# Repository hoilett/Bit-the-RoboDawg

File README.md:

# Bit-the-RoboDawg
Robot dog project

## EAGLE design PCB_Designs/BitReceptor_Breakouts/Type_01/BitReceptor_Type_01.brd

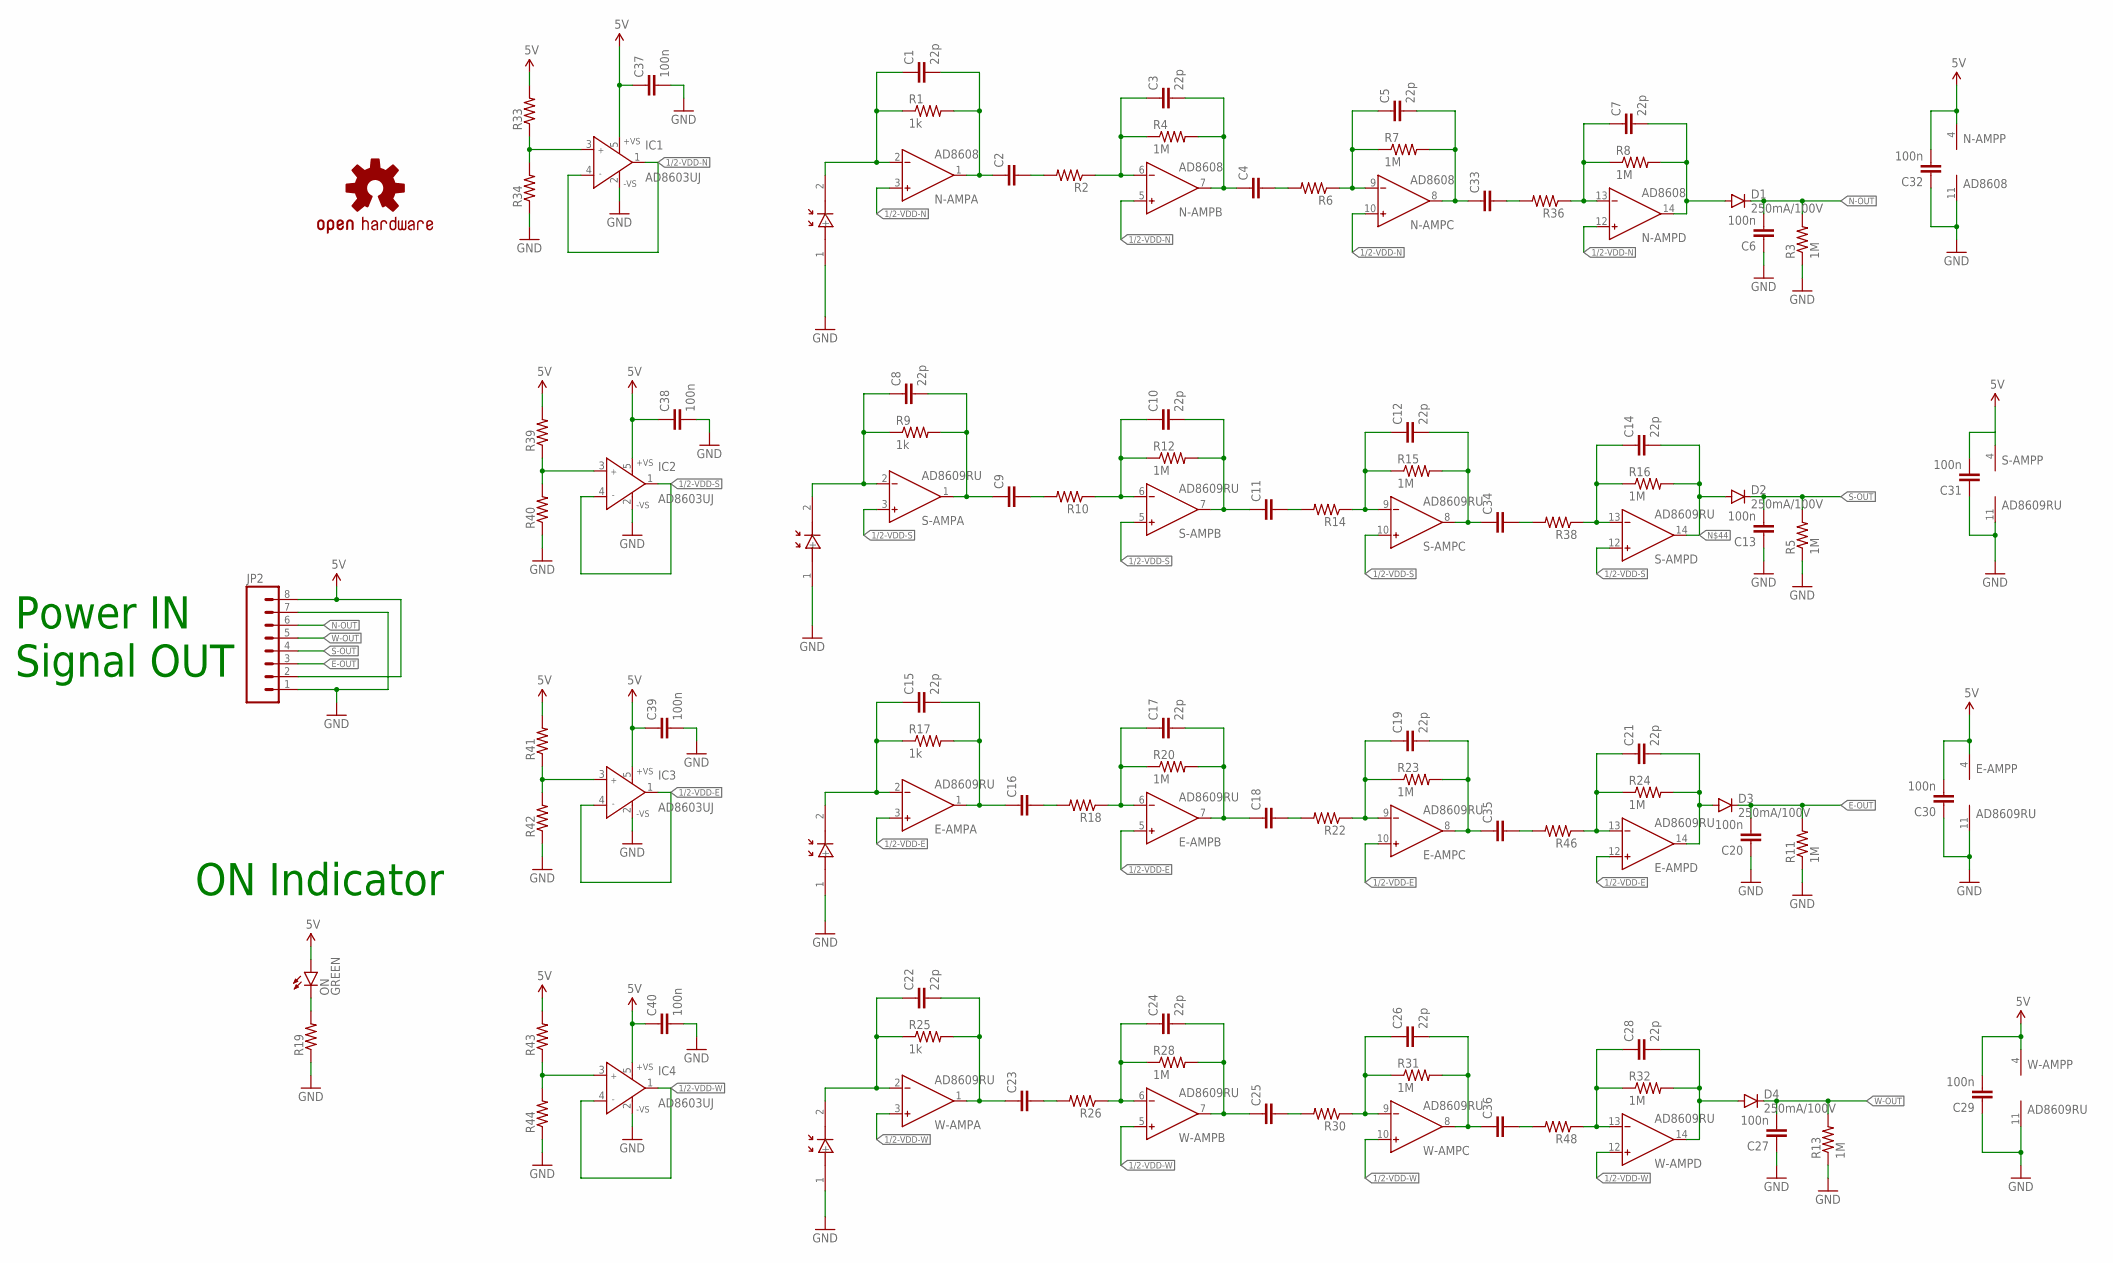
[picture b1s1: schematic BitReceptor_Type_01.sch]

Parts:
C1, C3, C5, C7, C8, C10, C12, C14, C15, C17, C19, C21, C22, C24, C26, C28: 22p; C0402
C2, C4, C9, C11, C16, C18, C23, C25, C33, C34, C35, C36: C-EUC0402; C0402
C6, C13, C20, C27, C29, C30, C31, C32, C37, C38, C39, C40: 100n; C0402
D1, D2, D3, D4: 250mA/100V; SOD-323
E-AMP: AD8609RU; TSSOP14
E-PD1: BPW46; PIN-PHOTODIODE
IC1, IC2, IC3, IC4: AD8603UJ; SOT23-5
JP2: M08NO_SILK; 1X08_PIN1_NO_SILK
LOGO1: OSHW-LOGOS; OSHW-LOGO-S
N-AMP: AD8608; TSSOP14
N-PD1: BPW46; PIN-PHOTODIODE
ON: GREEN; LED-0603
R1, R9, R17, R25: 1k; R0402
R2, R6, R10, R14, R18, R19, R22, R26, R30, R33, R34, R36, R38, R39, R40, R41, R42, R43, R44, R46, R48: R-US_R0402; R0402
R3, R4, R5, R7, R8, R11, R12, R13, R15, R16, R20, R23, R24, R28, R31, R32: 1M; R0402
S-AMP: AD8609RU; TSSOP14
S-PD1: BPW46; PIN-PHOTODIODE
W-AMP: AD8609RU; TSSOP14
W-PD1: BPW46; PIN-PHOTODIODE

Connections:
1/2-VDD-E: E-AMP.3 (IN+), E-AMP.5 (IN+), E-AMP.10 (IN+), E-AMP.12 (IN+), IC3.1 (OUT), IC3.4 (IN-)
1/2-VDD-N: IC1.1 (OUT), IC1.4 (IN-), N-AMP.3 (IN+), N-AMP.5 (IN+), N-AMP.10 (IN+), N-AMP.12 (IN+)
1/2-VDD-S: IC2.1 (OUT), IC2.4 (IN-), S-AMP.3 (IN+), S-AMP.5 (IN+), S-AMP.10 (IN+), S-AMP.12 (IN+)
1/2-VDD-W: IC4.1 (OUT), IC4.4 (IN-), W-AMP.3 (IN+), W-AMP.5 (IN+), W-AMP.10 (IN+), W-AMP.12 (IN+)
5V: C29.2, C30.2, C31.2, C32.2, C37.1, C38.1, C39.1, C40.1, E-AMP.4 (V+), IC1.5 (+VS), IC2.5 (+VS), IC3.5 (+VS), IC4.5 (+VS), JP2.2, JP2.8, N-AMP.4 (V+), ON.A, R33.2, R39.2, R41.2, R43.2, S-AMP.4 (V+), W-AMP.4 (V+)
E-OUT: C20.2, D3.C, JP2.3, R11.2
GND: C6.1, C13.1, C20.1, C27.1, C29.1, C30.1, C31.1, C32.1, C37.2, C38.2, C39.2, C40.2, E-AMP.11 (V-), E-PD1.1 (+), IC1.2 (-VS), IC2.2 (-VS), IC3.2 (-VS), IC4.2 (-VS), JP2.1, JP2.7, N-AMP.11 (V-), N-PD1.1 (+), R3.1, R5.1, R11.1, R13.1, R19.1, R34.1, R40.1, R42.1, R44.1, S-AMP.11 (V-), S-PD1.1 (+), W-AMP.11 (V-), W-PD1.1 (+)
unnamed: C1.1, N-AMP.2 (IN-), N-PD1.2 (-), R1.1
unnamed: C14.1, R16.1, R38.1, S-AMP.13 (IN-)
unnamed: C1.2, C2.1, N-AMP.1 (OUT), R1.2
unnamed: C8.1, R9.1, S-AMP.2 (IN-), S-PD1.2 (-)
unnamed: C3.1, N-AMP.6 (IN-), R2.1, R4.1
unnamed: C3.2, C4.1, N-AMP.7 (OUT), R4.2
unnamed: C5.1, N-AMP.9 (IN-), R6.1, R7.1
unnamed: C5.2, C33.1, N-AMP.8 (OUT), R7.2
unnamed: IC1.3 (IN+), R33.1, R34.2
unnamed: C7.1, N-AMP.13 (IN-), R8.1, R36.1
unnamed: C7.2, D1.A, N-AMP.14 (OUT), R8.2
unnamed: C10.1, R10.1, R12.1, S-AMP.6 (IN-)
unnamed: C10.2, C11.1, R12.2, S-AMP.7 (OUT)
unnamed: C12.1, R14.1, R15.1, S-AMP.9 (IN-)
unnamed: C12.2, C34.1, R15.2, S-AMP.8 (OUT)
unnamed: IC2.3 (IN+), R39.1, R40.2
unnamed: IC3.3 (IN+), R41.1, R42.2
unnamed: IC4.3 (IN+), R43.1, R44.2
unnamed: C15.1, E-AMP.2 (IN-), E-PD1.2 (-), R17.1
unnamed: C15.2, C16.1, E-AMP.1 (OUT), R17.2
unnamed: C17.1, E-AMP.6 (IN-), R18.1, R20.1
unnamed: C17.2, C18.1, E-AMP.7 (OUT), R20.2
unnamed: C19.1, E-AMP.9 (IN-), R22.1, R23.1
unnamed: C19.2, C35.1, E-AMP.8 (OUT), R23.2
unnamed: C28.1, R32.1, R48.1, W-AMP.13 (IN-)
unnamed: C21.1, E-AMP.13 (IN-), R24.1, R46.1
unnamed: C2.2, R2.2
unnamed: C22.1, R25.1, W-AMP.2 (IN-), W-PD1.2 (-)
unnamed: C22.2, C23.1, R25.2, W-AMP.1 (OUT)
unnamed: C24.1, R26.1, R28.1, W-AMP.6 (IN-)
unnamed: C24.2, C25.1, R28.2, W-AMP.7 (OUT)
unnamed: C26.1, R30.1, R31.1, W-AMP.9 (IN-)
unnamed: C26.2, C36.1, R31.2, W-AMP.8 (OUT)
unnamed: C4.2, R6.2
unnamed: C33.2, R36.2
unnamed: C34.2, R38.2
unnamed: C11.2, R14.2
unnamed: C9.2, R10.2
unnamed: C35.2, R46.2
unnamed: C18.2, R22.2
unnamed: C16.2, R18.2
unnamed: C36.2, R48.2
unnamed: C25.2, R30.2
unnamed: C14.2, D2.A, R16.2, S-AMP.14 (OUT)
unnamed: C23.2, R26.2
unnamed: C21.2, D3.A, E-AMP.14 (OUT), R24.2
unnamed: C28.2, D4.A, R32.2, W-AMP.14 (OUT)
unnamed: ON.C, R19.2
N-OUT: C6.2, D1.C, JP2.6, R3.2
S-AMP: C8.2, C9.1, R9.2, S-AMP.1 (OUT)
S-OUT: C13.2, D2.C, JP2.4, R5.2
W-OUT: C27.2, D4.C, JP2.5, R13.2

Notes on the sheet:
ON Indicator
Power IN Signal OUT

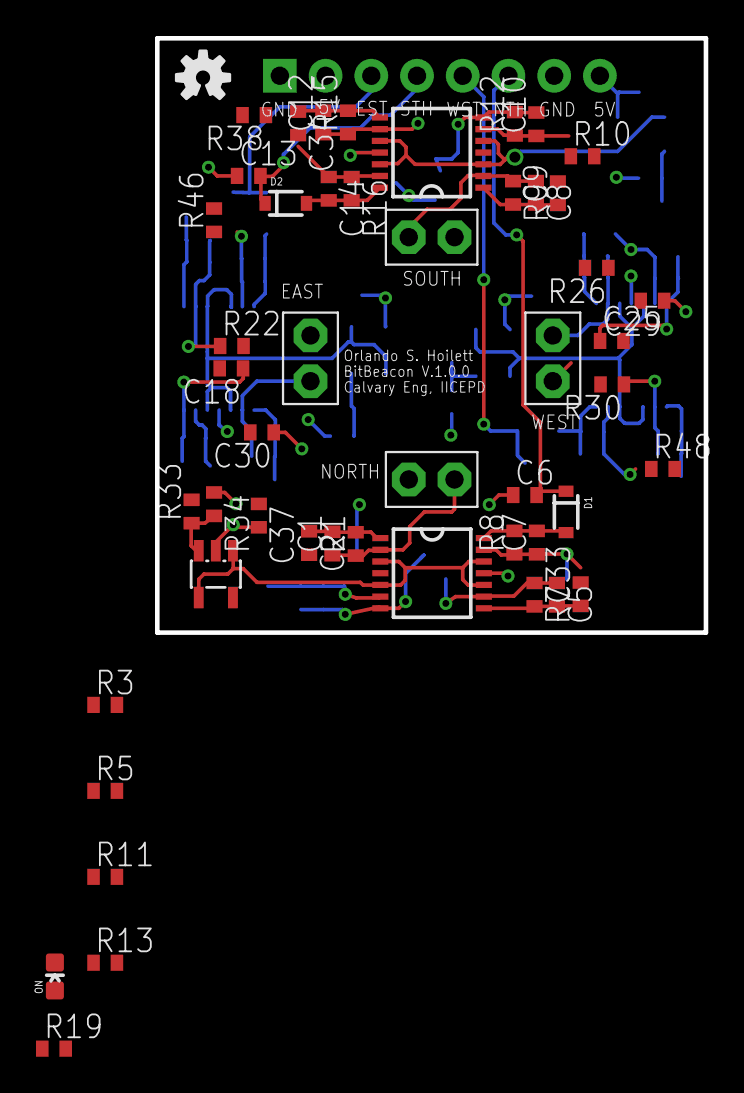
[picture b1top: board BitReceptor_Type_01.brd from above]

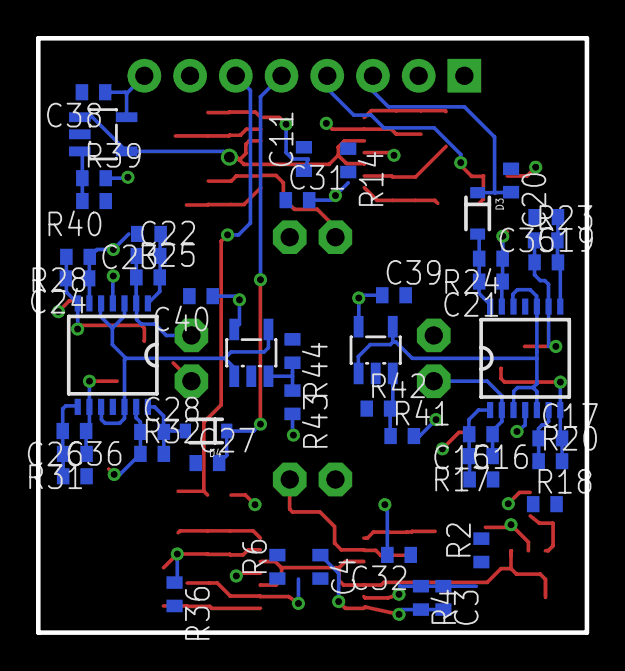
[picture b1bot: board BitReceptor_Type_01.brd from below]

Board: 2 copper layers, 30.5 x 33.0 mm, 100 parts (49 on the bottom side), 59 nets.

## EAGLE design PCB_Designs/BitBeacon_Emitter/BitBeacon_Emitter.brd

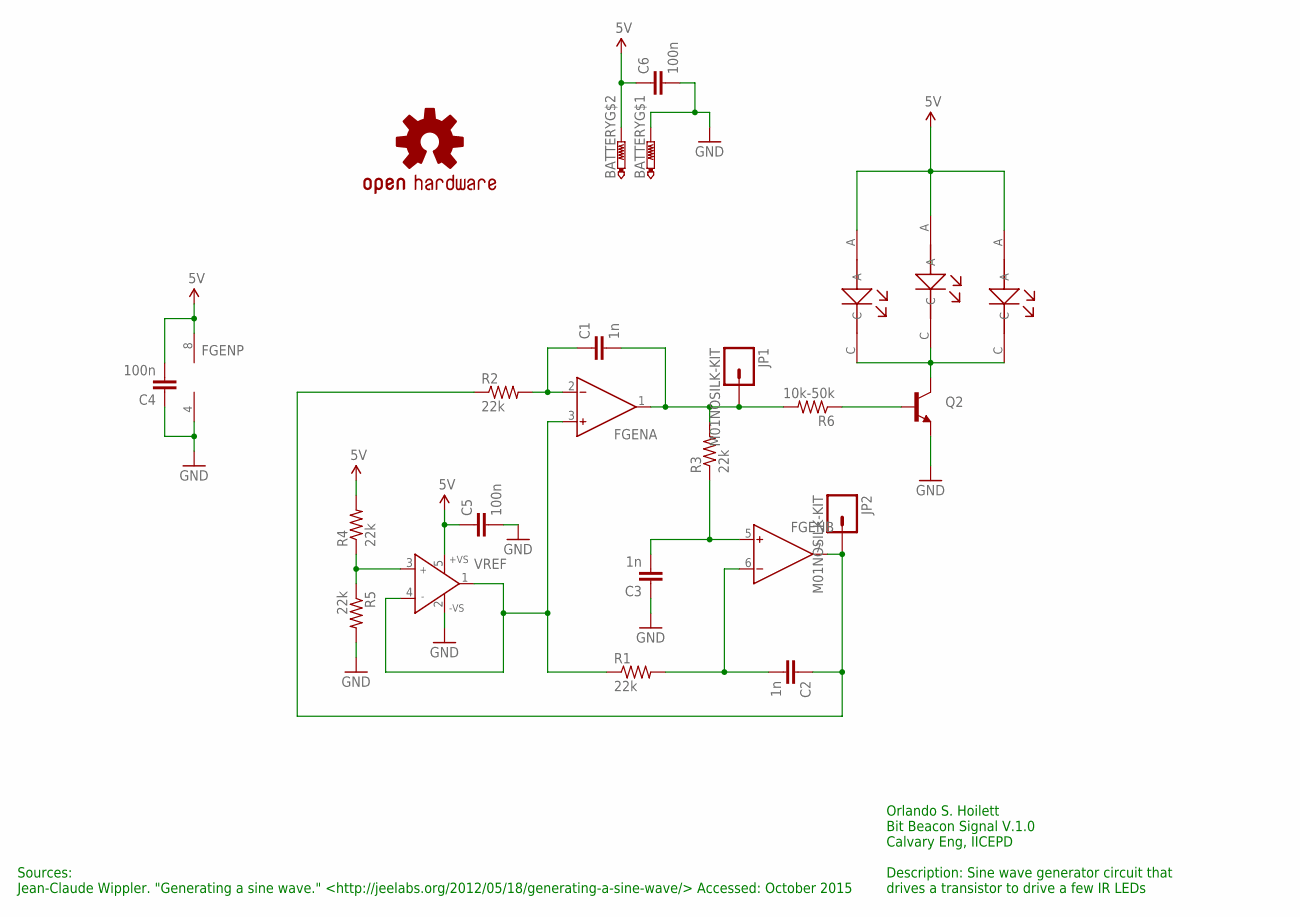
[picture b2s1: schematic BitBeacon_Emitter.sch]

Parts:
BATTERY: BATT-CONNECT; HOLE
C1, C2, C3: 1n; C0402
C4, C5, C6: 100n; C0402
FGEN: AD8607RM; MSOP08
JP1, JP2: M01NOSILK-KIT; 1X01NS-KIT
LED1, LED2, LED3: LED
LOGO1: OSHW-LOGOS; OSHW-LOGO-S
Q2: TRANSISTOR_NPN2N3904; TO-92
R1, R2, R3, R4, R5: 22k; R0402
R6: 10k-50k; R0402
VREF: AD8603UJ; SOT23-5

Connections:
5V: BATTERY.P$2, C4.2, C5.1, C6.1, FGEN.8 (V+), LED1.A, LED2.A, LED3.A, R4.2, VREF.5 (+VS)
COSINE: C2.1, FGEN.7 (OUT), JP2.1, R2.1
GND: BATTERY.P$1, C3.1, C4.1, C5.2, C6.2, FGEN.4 (V-), Q2.1 (E), R5.2, VREF.2 (-VS)
unnamed: C3.2, FGEN.5 (IN+), R3.1
unnamed: C1.1, FGEN.2 (IN-), R2.2
unnamed: C2.2, FGEN.6 (IN-), R1.2
unnamed: FGEN.3 (IN+), R1.1, VREF.1 (OUT), VREF.4 (IN-)
unnamed: R4.1, R5.1, VREF.3 (IN+)
unnamed: LED1.C, LED2.C, LED3.C, Q2.3 (C)
unnamed: Q2.2 (B), R6.1
SINE: C1.2, FGEN.1 (OUT), JP1.1, R3.2, R6.2

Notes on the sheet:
Orlando S. Hoilett Bit Beacon Signal V.1.0 Calvary Eng, IICEPD Description: Sine wave generator circuit that drives a transistor to drive a few IR LEDs
Sources: Jean-Claude Wippler. "Generating a sine wave." <http://jeelabs.org/2012/05/18/generating-a-sine-wave/> Accessed: October 2015

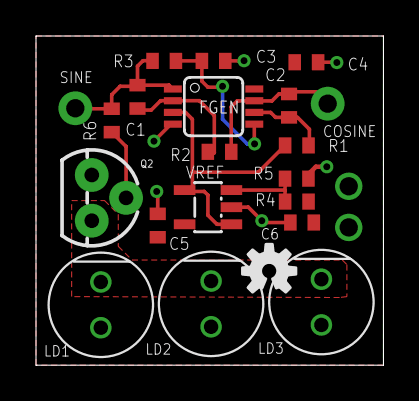
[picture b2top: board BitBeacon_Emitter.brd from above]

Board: 2 copper layers, 19.3 x 18.3 mm, 22 parts (0 on the bottom side), 11 nets.

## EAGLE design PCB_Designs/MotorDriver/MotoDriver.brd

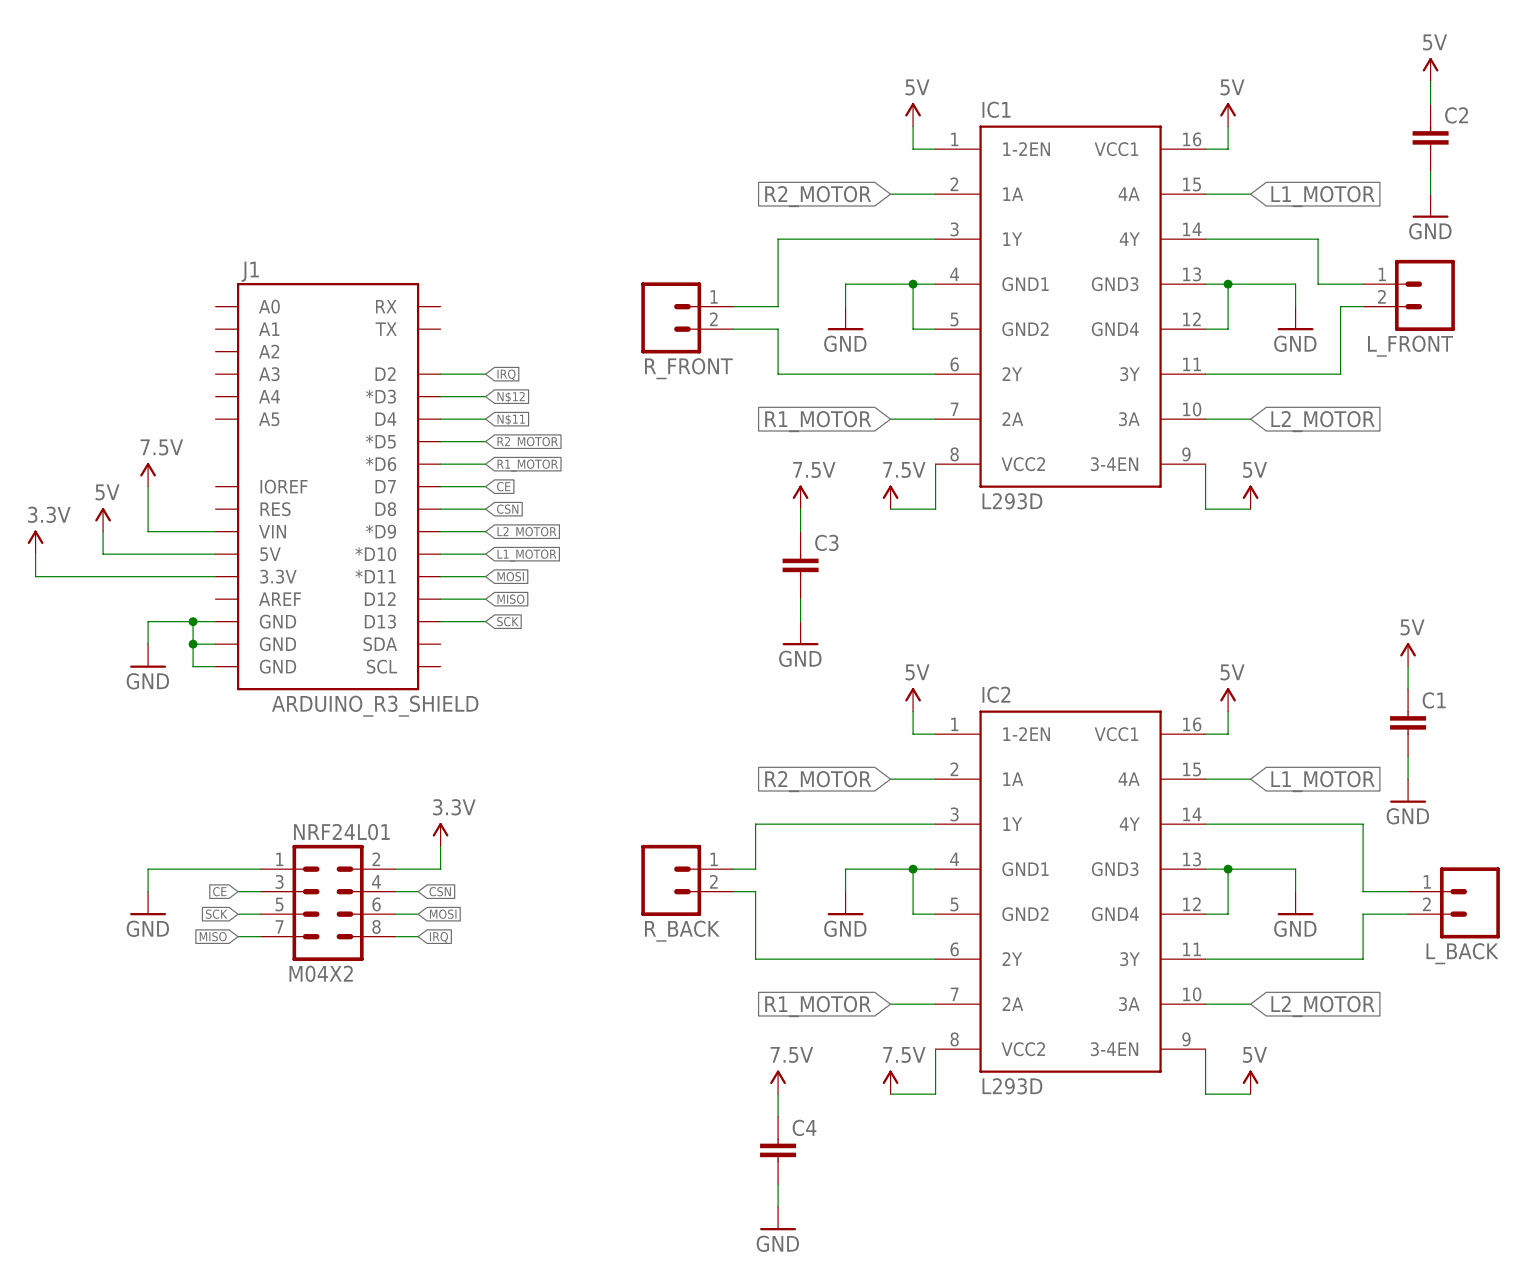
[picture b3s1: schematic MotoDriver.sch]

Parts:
C1, C2, C3, C4: C-EU050-024X044; C050-024X044
IC1, IC2: L293D; DIL16
J1: ARDUINO_R3_SHIELD; UNO_R3_SHIELD
L_BACK: M021X02_NO_SILK; 1X02_NO_SILK
L_FRONT: M021X02_NO_SILK; 1X02_NO_SILK
NRF24L01: M04X2; 2X4
R_BACK: M021X02_NO_SILK; 1X02_NO_SILK
R_FRONT: M021X02_NO_SILK; 1X02_NO_SILK

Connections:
3.3V: J1.3.3V, NRF24L01.2
5V: C1.1, C2.1, IC1.1 (1-2EN), IC1.9 (3-4EN), IC1.16 (VCC1), IC2.1 (1-2EN), IC2.9 (3-4EN), IC2.16 (VCC1), J1.5V
CE: J1.D7, NRF24L01.3
CSN: J1.D8, NRF24L01.4
GND: C1.2, C2.2, C3.2, C4.2, IC1.4 (GND1), IC1.5 (GND2), IC1.12 (GND4), IC1.13 (GND3), IC2.4 (GND1), IC2.5 (GND2), IC2.12 (GND4), IC2.13 (GND3), J1.GND@0 (GND), J1.GND@1 (GND), J1.GND@2 (GND), NRF24L01.1
IRQ: J1.D2, NRF24L01.8
L1_1: IC1.14 (4Y), L_FRONT.1
L1_2: IC2.14 (4Y), L_BACK.1
L1_MOTOR: IC1.15 (4A), IC2.15 (4A), J1.D10 (*D10)
L2_1: IC1.11 (3Y), L_FRONT.2
L2_2: IC2.11 (3Y), L_BACK.2
L2_MOTOR: IC1.10 (3A), IC2.10 (3A), J1.D9 (*D9)
MISO: J1.D12, NRF24L01.7
MOSI: J1.D11 (*D11), NRF24L01.6
R1_1: IC1.3 (1Y), R_FRONT.1
R1_2: IC2.3 (1Y), R_BACK.1
R1_MOTOR: IC1.7 (2A), IC2.7 (2A), J1.D6 (*D6)
R2_1: IC1.6 (2Y), R_FRONT.2
R2_2: IC2.6 (2Y), R_BACK.2
R2_MOTOR: IC1.2 (1A), IC2.2 (1A), J1.D5 (*D5)
SCK: J1.D13, NRF24L01.5
V_BATT: C3.1, C4.1, IC1.8 (VCC2), IC2.8 (VCC2), J1.VIN

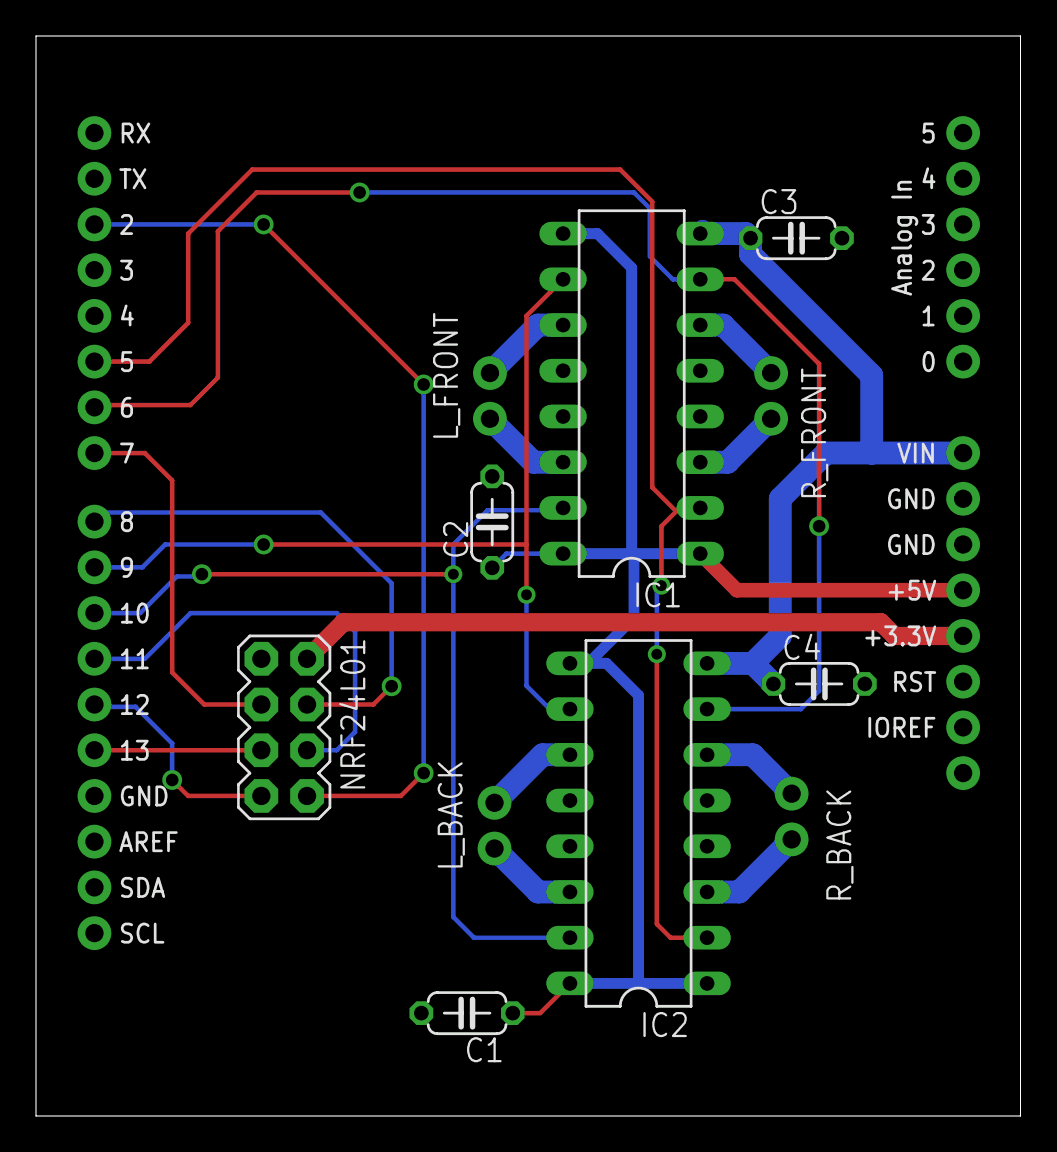
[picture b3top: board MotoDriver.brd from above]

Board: 2 copper layers, 54.7 x 60.0 mm, 12 parts (0 on the bottom side), 22 nets.

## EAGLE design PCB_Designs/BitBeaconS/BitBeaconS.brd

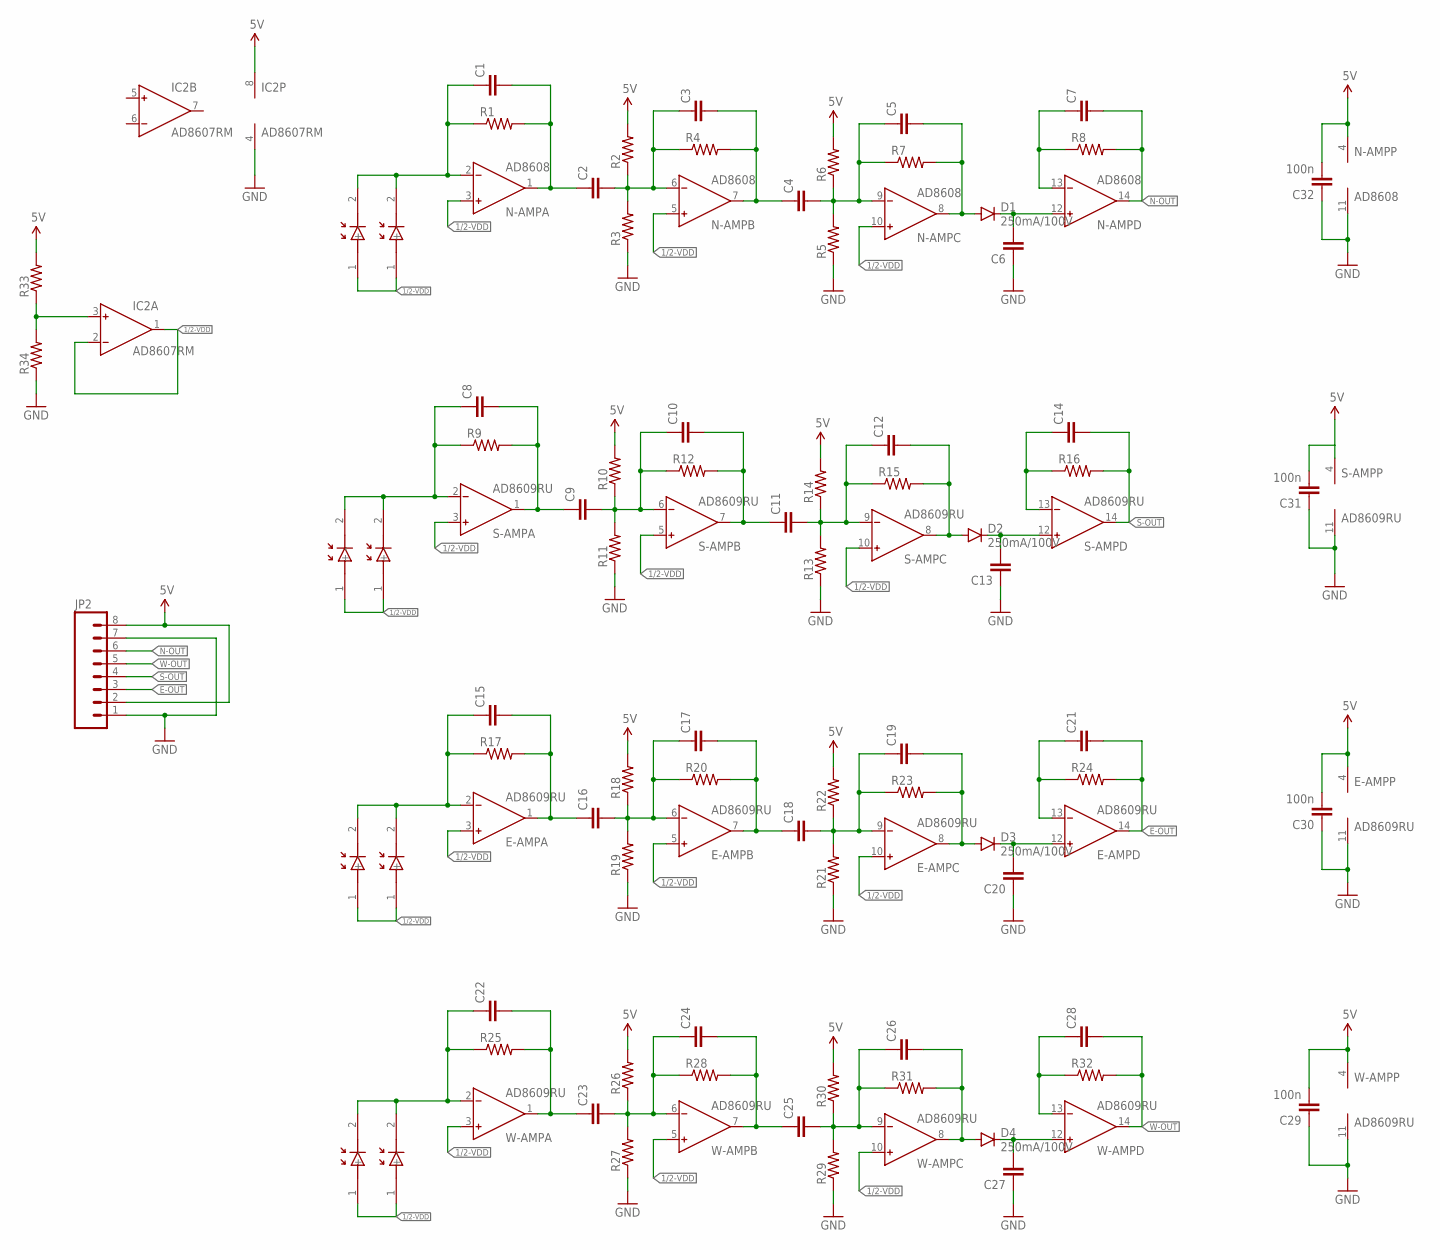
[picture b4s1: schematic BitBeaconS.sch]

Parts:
C1, C2, C3, C4, C5, C6, C7, C8, C9, C10, C11, C12, C13, C14, C15, C16, C17, C18, C19, C20, C21, C22, C23, C24, C25, C26, C27, C28: C-EUC0805; C0805
C29, C30, C31, C32: 100n; C0805
D1, D2, D3, D4: 250mA/100V; SOD-323
E-AMP: AD8609RU; TSSOP14
E-PD, E-PD1: BPW46; PIN-PHOTODIODE
IC2: AD8607RM; MSOP08
JP2: M08NO_SILK; 1X08_PIN1_NO_SILK
N-AMP: AD8608; TSSOP14
N-PD, N-PD1: BPW46; PIN-PHOTODIODE
R1, R2, R3, R4, R5, R6, R7, R8, R9, R10, R11, R12, R13, R14, R15, R16, R17, R18, R19, R20, R21, R22, R23, R24, R25, R26, R27, R28, R29, R30, R31, R32, R33, R34: R-US_R0805; R0805
S-AMP: AD8609RU; TSSOP14
S-PD, S-PD1: BPW46; PIN-PHOTODIODE
W-AMP: AD8609RU; TSSOP14
W-PD, W-PD1: BPW46; PIN-PHOTODIODE

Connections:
1/2-VDD: E-AMP.3 (IN+), E-AMP.5 (IN+), E-AMP.10 (IN+), E-PD.1 (+), E-PD1.1 (+), IC2.1 (OUT), IC2.2 (IN-), N-AMP.3 (IN+), N-AMP.5 (IN+), N-AMP.10 (IN+), N-PD.1 (+), N-PD1.1 (+), S-AMP.3 (IN+), S-AMP.5 (IN+), S-AMP.10 (IN+), S-PD.1 (+), S-PD1.1 (+), W-AMP.3 (IN+), W-AMP.5 (IN+), W-AMP.10 (IN+), W-PD.1 (+), W-PD1.1 (+)
5V: C29.2, C30.2, C31.2, C32.2, E-AMP.4 (V+), IC2.8 (V+), JP2.2, JP2.8, N-AMP.4 (V+), R2.2, R6.2, R10.2, R14.2, R18.2, R22.2, R26.2, R30.2, R33.2, S-AMP.4 (V+), W-AMP.4 (V+)
E-OUT: C21.2, E-AMP.14 (OUT), JP2.3, R24.2
GND: C6.1, C13.1, C20.1, C27.1, C29.1, C30.1, C31.1, C32.1, E-AMP.11 (V-), IC2.4 (V-), JP2.1, JP2.7, N-AMP.11 (V-), R3.1, R5.1, R11.1, R13.1, R19.1, R21.1, R27.1, R29.1, R34.1, S-AMP.11 (V-), W-AMP.11 (V-)
unnamed: C1.1, N-AMP.2 (IN-), N-PD.2 (-), N-PD1.2 (-), R1.1
unnamed: C6.2, D1.C, N-AMP.12 (IN+)
unnamed: C1.2, C2.1, N-AMP.1 (OUT), R1.2
unnamed: C8.1, R9.1, S-AMP.2 (IN-), S-PD.2 (-), S-PD1.2 (-)
unnamed: C2.2, C3.1, N-AMP.6 (IN-), R2.1, R3.2, R4.1
unnamed: C3.2, C4.1, N-AMP.7 (OUT), R4.2
unnamed: C4.2, C5.1, N-AMP.9 (IN-), R5.2, R6.1, R7.1
unnamed: C5.2, D1.A, N-AMP.8 (OUT), R7.2
unnamed: IC2.3 (IN+), R33.1, R34.2
unnamed: C7.1, N-AMP.13 (IN-), R8.1
unnamed: C9.2, C10.1, R10.1, R11.2, R12.1, S-AMP.6 (IN-)
unnamed: C10.2, C11.1, R12.2, S-AMP.7 (OUT)
unnamed: C11.2, C12.1, R13.2, R14.1, R15.1, S-AMP.9 (IN-)
unnamed: C12.2, D2.A, R15.2, S-AMP.8 (OUT)
unnamed: C13.2, D2.C, S-AMP.12 (IN+)
unnamed: C14.1, R16.1, S-AMP.13 (IN-)
unnamed: C15.1, E-AMP.2 (IN-), E-PD.2 (-), E-PD1.2 (-), R17.1
unnamed: C15.2, C16.1, E-AMP.1 (OUT), R17.2
unnamed: C16.2, C17.1, E-AMP.6 (IN-), R18.1, R19.2, R20.1
unnamed: C17.2, C18.1, E-AMP.7 (OUT), R20.2
unnamed: C18.2, C19.1, E-AMP.9 (IN-), R21.2, R22.1, R23.1
unnamed: C19.2, D3.A, E-AMP.8 (OUT), R23.2
unnamed: C20.2, D3.C, E-AMP.12 (IN+)
unnamed: C21.1, E-AMP.13 (IN-), R24.1
unnamed: C22.1, R25.1, W-AMP.2 (IN-), W-PD.2 (-), W-PD1.2 (-)
unnamed: C22.2, C23.1, R25.2, W-AMP.1 (OUT)
unnamed: C23.2, C24.1, R26.1, R27.2, R28.1, W-AMP.6 (IN-)
unnamed: C24.2, C25.1, R28.2, W-AMP.7 (OUT)
unnamed: C25.2, C26.1, R29.2, R30.1, R31.1, W-AMP.9 (IN-)
unnamed: C26.2, D4.A, R31.2, W-AMP.8 (OUT)
unnamed: C27.2, D4.C, W-AMP.12 (IN+)
unnamed: C28.1, R32.1, W-AMP.13 (IN-)
N-OUT: C7.2, JP2.6, N-AMP.14 (OUT), R8.2
S-AMP: C8.2, C9.1, R9.2, S-AMP.1 (OUT)
S-OUT: C14.2, JP2.4, R16.2, S-AMP.14 (OUT)
W-OUT: C28.2, JP2.5, R32.2, W-AMP.14 (OUT)

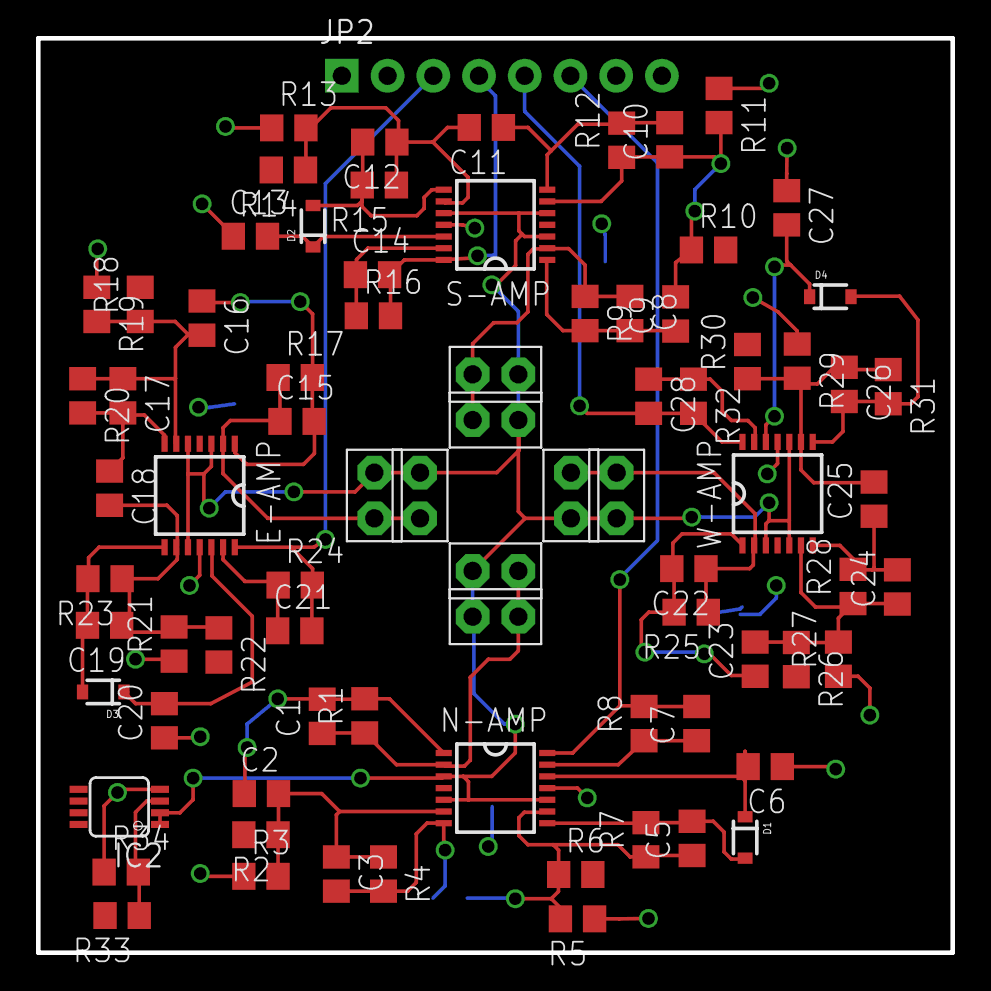
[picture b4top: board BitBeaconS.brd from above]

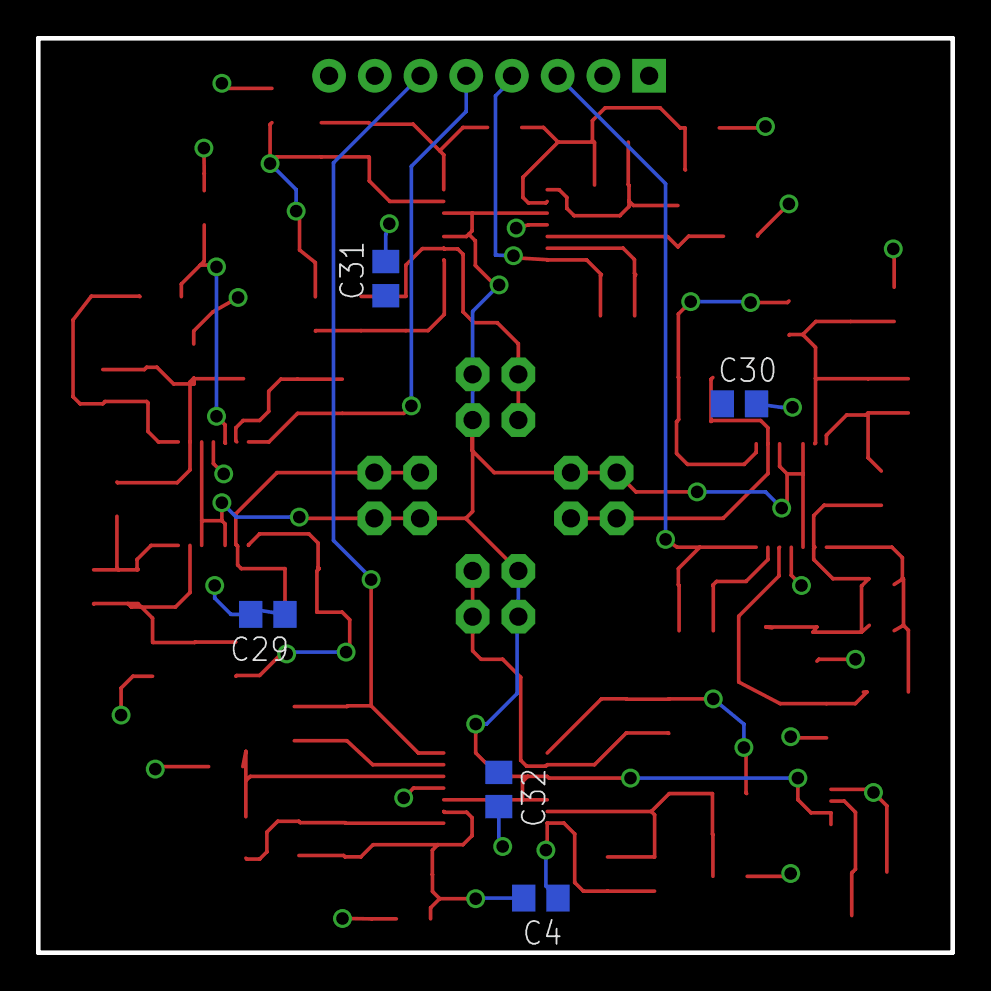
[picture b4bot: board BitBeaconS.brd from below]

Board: 2 copper layers, 50.8 x 50.8 mm, 84 parts (5 on the bottom side), 40 nets.

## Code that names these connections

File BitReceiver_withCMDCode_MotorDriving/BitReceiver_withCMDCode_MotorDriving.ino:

/*
 * Shadman Jubaer and Orlando Hoilett
 * 
 * Project Title: Bit the RoboCar
 * 
 * Description
 * We created a remote controlled car using two nRF24L01 RF
 * transceiver modules. An Arduino reads the directeion values
 * from a joystick and sends the instructions to another Arduino
 * to control a robot chassis.
 * 
 */


#include <SPI.h>
#include <nRF24L01.h>
#include <RF24.h>
#include <RF24_config.h>

int l1_motor = 10;
int l2_motor = 9;
int r1_motor = 6;
int r2_motor = 5; 


int messageLength = 12;
int msg[1];
RF24 radio(7,8);
const uint64_t pipe = 0xE8E8F0F0E1LL;
int lastmsg = 1;
String theMessage = "";
char theChar = 0;

int xBuffer[5];
int yBuffer[5];
int bufferVal = 0;
int xDir;
int yDir;
int buttonVal;


int zeroLine = 50;

void setup(void)
{
  Serial.begin(115200);
  radio.begin();
  radio.openReadingPipe(1,pipe);
  radio.startListening();
      Serial.println("STOP");
      analogWrite(l2_motor, 0);
      analogWrite(l1_motor, 0);
      
      analogWrite(r1_motor, 0);
      analogWrite(r2_motor, 0);
}

void loop(void)
{
  while(!radio.available());
  radio.read(msg, 1);
  theChar = msg[0];
  
  if(msg[0] == '*'){
    radio.read(msg, 1);
    theChar = msg[0];
    
    while(msg[0] != '&'){
      
      if (theChar != NULL){
      theMessage.concat(theChar);
      }
      
      radio.read(msg, 1);
      theChar = msg[0];
    }

     if (bufferVal <= 4){
      
      int delimiter = theMessage.indexOf(',');
      int delimiter2 = theMessage.indexOf(',', (delimiter+1));
      int length = theMessage.length();
      char charBuf[length];
      
      theMessage.substring(0,delimiter).toCharArray(charBuf,length);
      buttonVal = atof(charBuf);
      
      theMessage.substring(delimiter+1, delimiter2).toCharArray(charBuf,length);
      xBuffer[bufferVal] = (int)atof(charBuf);
      //Serial.print(xBuffer[bufferVal]); Serial.print('\t');
      
  
      theMessage.substring(delimiter2+1, theMessage.length()).toCharArray(charBuf,length);
      yBuffer[bufferVal] = (int)atof(charBuf);
      //Serial.print(yBuffer[bufferVal]);
      //Serial.print('\t');
      
      //Filter out noise due to high numbers 
      if (xBuffer[bufferVal] <= 1023 && xBuffer[bufferVal] >= 0 && yBuffer[bufferVal] <= 1023 && yBuffer[bufferVal] >= 0)
      {
        bufferVal = bufferVal + 1;
      }

      //Filter out noise due to random shifts
      if(bufferVal >= 2 && xBuffer[bufferVal] == xBuffer[bufferVal-2])
      {
        if (xBuffer[bufferVal-1] != xBuffer[bufferVal] && xBuffer[bufferVal-1] != xBuffer[bufferVal-2])
        {
          xBuffer[bufferVal-1] = xBuffer[bufferVal]; 
        }
        if (yBuffer[bufferVal-1] != yBuffer[bufferVal] && yBuffer[bufferVal-1] != yBuffer[bufferVal-2])
        {
          yBuffer[bufferVal-1] = yBuffer[bufferVal]; 
        } 
      }
     }
     
    else {   
      bufferVal = 0;
      xDir = (xBuffer[0] + xBuffer[1] + xBuffer[2] + xBuffer[3] + xBuffer[4])/5;
      //Serial.print(xDir); Serial.print('\t');
      yDir = (yBuffer[0] + yBuffer[1] + yBuffer[2] + yBuffer[3] + yBuffer[4])/5;
      //Serial.println(yDir);
      //Serial.print('\t');
      
      if (xDir <= 1023 && yDir <= 1023){
        xDir = map(xDir, 0, 1023, -255, 255);
        //Serial.print(xDir); Serial.print('\t');
        yDir = map(yDir, 0, 1023, -255, 255);
        //Serial.println(yDir);
      }
    }
  
    int diff = abs(xDir) - abs(yDir);

    //GO FORWARD
    if(xDir > zeroLine){
      Serial.println("FORWARD");
      analogWrite(l1_motor, xDir);
      analogWrite(l2_motor, 0);
      
      analogWrite(r1_motor, xDir);
      analogWrite(r2_motor, 0);
    }

    //GO BACKWARD
    else if(xDir < -zeroLine){
      Serial.println("BACKWARD");
      analogWrite(l2_motor, abs(xDir));
      analogWrite(l1_motor, abs(0));
      
      analogWrite(r2_motor, abs(xDir));
      analogWrite(r1_motor, abs(0));
    }
    
    //TURN RIGHT
    if(yDir > zeroLine){
      Serial.println("RIGHT");
      analogWrite(l1_motor, yDir);
      analogWrite(l2_motor, 0);
      
      analogWrite(r1_motor, 0);
      analogWrite(r2_motor, yDir);
    }

    //TURN LEFT
    else if(yDir < -zeroLine){
      Serial.println("LEFT");
      analogWrite(l2_motor, abs(yDir));
      analogWrite(l1_motor, abs(0));
      
      analogWrite(r2_motor, 0);
      analogWrite(r1_motor, abs(yDir));
    }

    //STOP
    else if (abs(yDir) < abs(zeroLine) && abs(xDir) < abs(zeroLine) ){
      Serial.println("STOP");
      analogWrite(l2_motor, 0);
      analogWrite(l1_motor, 0);
      
      analogWrite(r1_motor, 0);
      analogWrite(r2_motor, 0);      
    }
  }  
  //    //Serial.println(theMessage);
  //    Serial.print(buttonVal); Serial.print('\t');
  //    Serial.print(xDir); Serial.print('\t');
  //    Serial.println(yDir);
    theMessage = "";
    //delay(1);
}

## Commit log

2016-03-27 Version 0.3.1 of light receiver for direction control
2016-03-27 Version 0.0.5 of Bit software. Prototyping for responding to light source and moving that direction
2016-04-19 updating project plan
2016-04-19 controlling robot chassis with nRF24L01 modules
2016-04-19 Adding radio functionality
2016-04-19 updated BitDriverRadio code to note which motor controls which wheel; updated ProjectPlan with a bit more description
2016-04-19 Some more radio
2016-04-19 First commit on radio sender
2016-04-19 Added files via upload
2016-04-20 Added code to create send radio data. No idea if it works yet.
2016-04-20 Folder structure
2016-04-20 Small fixes to radio transmit code
2016-04-25 Added receiver with motor control file
2016-04-25 Added forward and reverse driving
2016-04-25 Averaged xy values
2016-04-25 adding new pcb file for milling machine
2016-04-25 adding turning function
2016-04-25 debugged averaging algorithm
2016-04-25 added turning code
2016-04-26 Added some extra noise filtering and hopefully smoothed the steering
2016-04-26 Turns well and smooth!
2016-05-01 added gitignore file to prevent adding Gerber files
2016-05-01 finishing up PCB
2016-05-01 deleted MotoDriver Gerber files from git
2016-05-01 removing .DS_Store files
2016-05-01 added a few descriptions before submitting code for 595 Project
2016-05-01 updating controlling bit with light sensors
2016-05-01 finished Bit Beacon design
2016-05-01 testing excluding .b#x and .s#x files
2016-05-01 removed .b#x and .s#x files
2016-05-01 finished and ordered PCB design for Bit Beacon
2016-05-01 added .zip file containing Gerber files that were generated to order BitBeacon V.1.0.0 from OSH Park May 1, 2016
2016-05-03 updating BitBeacon design with a better high pass filter design and started teh BitBeacon_Emitter circuit
2016-05-04 updating pcb files for emitter circuit
2016-05-05 added datasheets for photosensors
2016-05-07 finished PCB design for Bit Beacon Emitter circuit and added datsheets for the LEDs that I think would work well.
2016-05-19 updated Bit emitter PCB design with resistor and capacitor values. Added a bill of materials for BitBeacon and BitBeacon_Emitter
2016-05-19 deleted Bit_Beacon directory and replaced with BitBeacon directory
2016-05-19 deleted .b#x and .s#x files
2016-05-21 added LCD code
2016-05-22 okay going north, north-east, and east
2016-05-22 added resistor to peak detector circuit to discharge capacitor
2016-05-22 updates to beacon emitter design
2016-05-23 corrections to PCB for BitBeacon, updates on BitController
2016-05-23 updates to code to include Bluetooth, updates to BitBeacon circuit to include labels, indicator LEDs, added BitBeacon Breakout to prototype different signal amplifier types
2016-05-24 added a list of helpful git commands. also added a project log file to keep track of what we do
2016-05-25 added a link to an online git cheat sheet
2016-05-25 updates moving back to if statements to control movement
2016-05-25 updates runs well
2016-05-26 controller code appears to be pretty smooth. Also updated ProjectLog with details on the day
2016-05-27 updated log and project plan
2016-05-28 removed AFMotor library, updated comments and descriptions for BitController, and updated ProjectLog
2016-05-28 changed the name of each Bill of Materials documents and added a folder for Pictures and Videos
2016-05-28 deleted old bill of materials files
2016-06-02 test codes to add bluetooth and ultrasonic distance sensor to Bit
2016-06-11 made minor changes to BitBeacon
2016-06-11 started adding to Bit Motor Driver Bill of Materials (BOM)
2016-06-11 added ON indicator LED for power and pull down resistor for peak detector circuit
2016-06-11 added pictures and videos documenting work and showing demos
2016-06-11 changed name of photosensor circuit to BitReceptor instead of BitBeacon which is now the name of the LED emitting circuit
2016-06-11 updating controller code to include a filter to deal with reflection of light from BitBeacon off of reflective surfaces
2016-06-11 deleted BitBeacon_Breakouts due to name change of photosensor circuit to BitReceptor and LED emitter circuit
2016-06-11 updated project log
2016-06-11 removed .b#x filie
2016-06-11 created Bill-of-Materials folder
2016-06-13 added circuit diagram for version 2 of BitBeacon
2016-06-18 updates to project log
2016-06-23 went back to stable version of the BitController; the Queue class is not utilized

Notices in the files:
parts and their libraries:
SparkFun-Connectors: Licensing: Creative Commons ShareAlike 4.0 International - https://creativecommons.org/licenses/by-sa/4.0
